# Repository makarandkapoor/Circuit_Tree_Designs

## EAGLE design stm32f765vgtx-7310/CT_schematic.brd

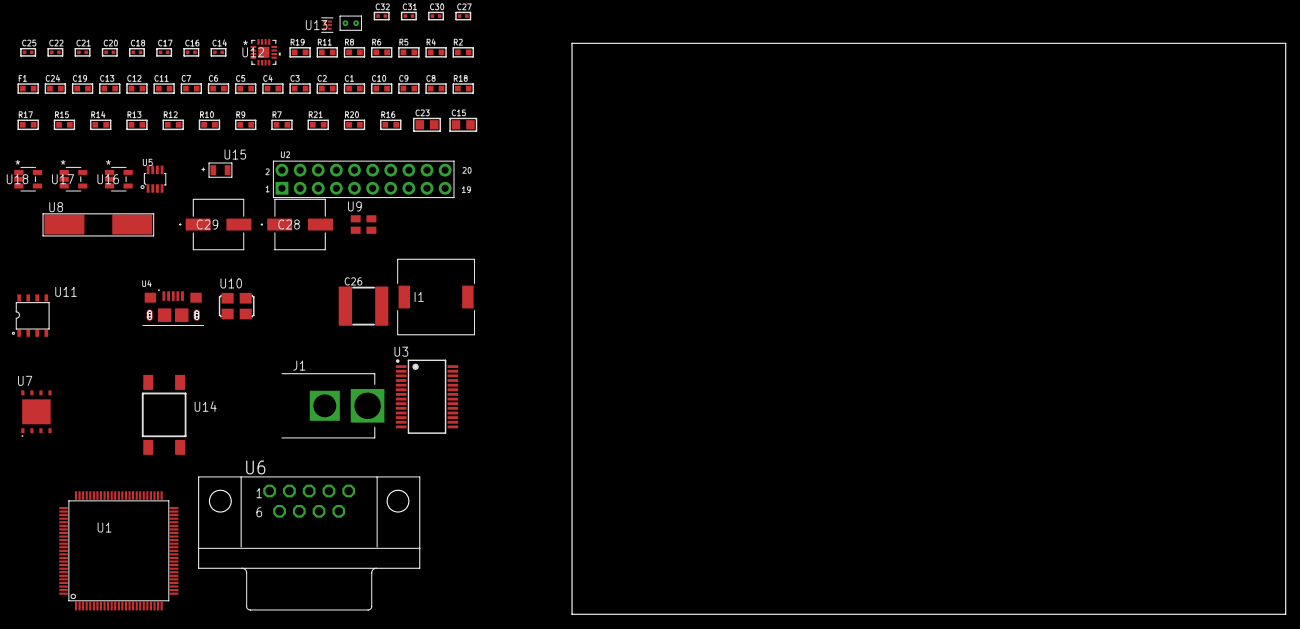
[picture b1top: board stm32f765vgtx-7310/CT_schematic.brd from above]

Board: 2 copper layers, 73 parts (0 on the bottom side), 57 nets, no tracks yet.

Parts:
C1, C12, C13, C19, C24: 1e-06; C0603
C2, C3, C4, C5, C6, C7: 1e-07; C0603
C8: 4.7e-06; C0603
C9, C10: 2.2e-06; C0603
C11: 1e-08; C0603
C14, C16, C17, C18, C25, C27: 1e-07; C0402
C15: 4.7e-06; C0805
C20, C21, C22, C30, C31, C32: 1e-08; C0402
C23: 1e-05; C0805
C26: 6.8e-05; 2220
C28, C29: 0.0001; EXV-9H
F1: 240.0; L0603
I1: 3.8e-06; DR1040
J1: PJ-037B; PJ-037B_PACKAGE
R2: 1000.0; R0603
R4, R5, R6, R8: 4700.0; R0603
R7, R9, R10, R12, R13, R17, R18: 10000.0; R0603
R11: 120.0; R0603
R14: 20000.0; R0603
R15: 91000.0; R0603
R16: 300000.0; R0603
R19: 9100.0; R0603
R20: 680000.0; R0603
R21: 120000.0; R0603
U1: STM32F765VGT6; LQFP100
U2: arducam_ov2640; ARDUCAM
U3: FT232RL-REEL; SSOP-28
U4: 10118193-0001LF; FCI_10118193-0001LF
U5: MAX3051EKA+T; SOT-23-8
U6: 182-009-113R531; 182-009-MALE
U7: MX25R6435FZAIH0; WSON-8-PAD
U8: ABLS-12.000MHZ-B4-T
U9: ASEK-32.768KHz-ECST; ASEK
U10: ASFL1-25MHZ-NCS; ASFL1
U11: idt74fct38072; IDT74FCT38072
U12: LTC3601EUD#PBF; QFN-16_EP
U13: TPS3895ADRYR; SON-6
U14: 4-1437565-2; SW_4-1437565-2
U15: Q65110A2395; LGM67K-G1J2-24-Z
U16, U17, U18: nc7sz125m5x; NC7SZ125M5X
U19: Dummy; DUMMY_PACKAGE_160

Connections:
CLK_CRYSTAL_U3_27: U3.27, U8.1
CLK_CRYSTAL_U3_28: U3.28, U8.2
CLK_U1_8: U1.8, U9.3
CLK_U1_12: U1.12, U11.6
CLK_U2_8: U2.8, U11.7
CLK_U11_3: U10.3, U11.3
GND: C1.2, C2.2, C3.2, C4.2, C5.2, C6.2, C7.2, C8.2, C9.2, C10.2, C11.2, C12.2, C13.2, C14.2, C15.2, C16.2, C17.2, C18.2, C19.2, C20.2, C21.2, C22.2, C23.2, C24.2, C26.1, C26.2, C27.2, C28.2, C29.2, C30.2, C31.2, C32.2, J1.2, R2.2, R7.2, R10.2, R14.2, R16.2, R19.2, R21.2, U1.10, U1.19, U1.26, U1.49, U1.74, U1.99, U2.2, U2.20, U3.7, U3.18, U3.21, U3.25, U3.26, U4.5, U4.6, U4.7, U4.8, U4.9, U5.2, U5.8, U6.5, U7.4, U7.PAD, U9.2, U10.2, U11.4, U11.5, U11.8, U12.1, U12.9, U12.17, U13.2, U15.C, U16.1, U16.3, U17.1, U17.3, U18.1, U18.3, U19.1
NET_U1_14: R5.1, U1.14, U17.4
NET_U1_21: C11.1, C12.1, F1.1, U1.20, U1.21
NET_U1_48: C9.1, U1.48
NET_U1_73: C10.1, U1.73
NET_U1_94: R7.1, U1.94
NET_U1_98: U14.3, U14.4
NET_U2_19: R6.1, U2.19, U18.4
NET_U3_14: R9.1, U3.14
NET_U3_17: C16.1, U3.17
NET_U3_19: R10.1, U3.19
NET_U4_1: R8.1, U4.1
NET_U4_2: U3.16, U4.2
NET_U4_3: U3.15, U4.3
NET_U5_6: R11.2, U5.6
NET_U6_2: R11.2, U5.6, U6.2
NET_U6_3: R11.1, U5.7, U6.3
NET_U7_7: R4.1, U1.23, U7.7, U16.4
NET_U12_3: C25.2, I1.1, U12.3, U12.4
NET_U12_6: C25.1, U12.6
NET_U12_7: C24.1, U12.7, U12.12
NET_U12_10: R16.1, U12.10
NET_U12_11: R14.1, R15.1, U12.11
NET_U12_ATNET_3: I1.2, R15.2
NET_U13_1: R18.1, R19.1, U13.1
NET_U13_3: R20.2, R21.1, U13.3
NET_U13_4: R17.1, U13.4, U16.2, U17.2, U18.2
NET_U14_1: R2.1, U14.1, U14.2
PROC_CAN1_RX: U1.70, U5.4
PROC_CAN1_TX: U1.71, U5.1
PROC_DAC_OUT2: U1.29, U19.2
PROC_DCMI_D0: U1.63, U2.18
PROC_DCMI_D1: U1.64, U2.17
PROC_DCMI_D2: U1.65, U2.16
PROC_DCMI_D3: U1.66, U2.15
PROC_DCMI_D4: U1.3, U2.14
PROC_DCMI_D5: U1.84, U2.13
PROC_DCMI_D6: U1.4, U2.12
PROC_DCMI_D7: U1.5, U2.11
PROC_DCMI_D8: U1.78, U2.10
PROC_DCMI_D9: U1.80, U2.9
PROC_DCMI_HSYNC: U1.28, U2.6
PROC_DCMI_PIXCLK: U1.30, U2.7
PROC_DCMI_VSYNC: U1.93, U2.5
PROC_QUADSPI_BK1_IO0: U1.58, U7.5
PROC_QUADSPI_BK1_IO1: U1.59, U7.2
PROC_QUADSPI_BK1_IO2: R13.1, U1.1, U7.3
PROC_QUADSPI_BK1_NCS: R12.1, U1.46, U7.1
PROC_QUADSPI_CLK: U1.36, U7.6
VCC_S1_8V7: C23.1, C28.1, C29.1, J1.1, U12.15, U12.16
VCC_TIER1_3V3: C1.1, C2.1, C3.1, C4.1, C5.1, C6.1, C7.1, C8.1, C13.1, C14.1, C15.1, C17.1, C18.1, C19.1, C20.1, C21.1, C22.1, C26.2, C27.1, C30.1, C31.1, C32.1, F1.2, I1.2, R4.2, R5.2, R6.2, R9.2, R12.2, R13.2, R15.2, R17.2, R18.2, R20.1, U1.6, U1.11, U1.27, U1.50, U1.75, U1.100, U2.1, U3.4, U3.20, U5.3, U7.8, U9.4, U10.4, U11.1, U11.2, U12.8, U13.6, U16.5, U17.5, U18.5

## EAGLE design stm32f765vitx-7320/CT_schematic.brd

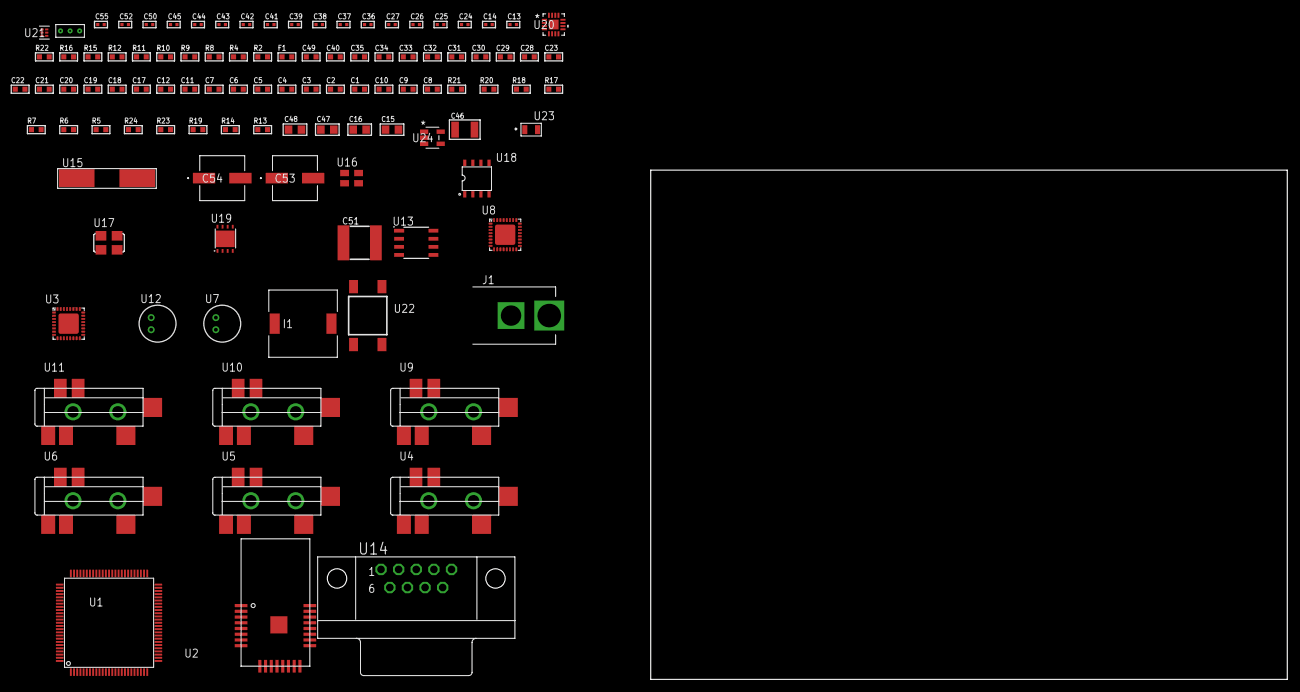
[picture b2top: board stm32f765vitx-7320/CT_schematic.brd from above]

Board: 2 copper layers, 100.0 x 80.0 mm, 105 parts (0 on the bottom side), 75 nets, no tracks yet.

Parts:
C1, C12, C17, C18, C19, C20, C21, C22, C23, C28, C29, C30, C31, C32, C33, C34, C35, C40, C49: 1e-06; C0603
C2, C3, C4, C5, C6, C7: 1e-07; C0603
C8: 4.7e-06; C0603
C9, C10: 2.2e-06; C0603
C11: 1e-08; C0603
C13, C14: 1e-11; C0402
C15, C16, C47, C48: 1e-05; C0805
C24, C25, C26, C27, C36, C37, C38, C39, C41, C50, C52: 1e-07; C0402
C42, C43, C44, C45, C55: 1e-08; C0402
C46: 1e-05; C1210
C51: 6.8e-05; 2220
C53, C54: 0.0001; EXV-9H
F1: 240.0; L0603
I1: 3.8e-06; DR1040
J1: PJ-037B; PJ-037B_PACKAGE
R2, R16: 1000.0; R0603
R4: 4700.0; R0603
R5, R6, R7, R20, R21: 10000.0; R0603
R8, R9, R10, R11: 1270.0; R0603
R12: 120.0; R0603
R13, R14: 100000.0; R0603
R15: 200.0; R0603
R17: 20000.0; R0603
R18: 91000.0; R0603
R19: 300000.0; R0603
R22: 9100.0; R0603
R23: 680000.0; R0603
R24: 120000.0; R0603
U1: STM32F765VIT6; LQFP100
U2: ATBTLC1000-MR110CA
U3, U8: SGTL5000XNAA3; QFN-32
U4, U5, U6, U9, U10, U11: SJ-43515TS-SMT-TR
U7, U12: WM-64PCT; WM-64PC
U13: SN65HVD230D; SOIC-8
U14: 182-009-113R531; 182-009-MALE
U15: ABLS-25.000MHZ-B2F-T
U16: ASEK-32.768KHz-ECST; ASEK
U17: ASFL-24.57MHZ-NCS; ASFL1
U18: idt74fct38072; IDT74FCT38072
U19: LP3878SDX-ADJ/NOPB; WSON-8
U20: LTC3601EUD#PBF; QFN-16_EP
U21: TPS3895ADRYR; SON-6
U22: 4-1437565-2; SW_4-1437565-2
U23: Q65110A2395; LGM67K-G1J2-24-Z
U24: nc7sz125m5x; NC7SZ125M5X
U25: Dummy; DUMMY_PACKAGE_213

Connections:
CLK_CRYSTAL_U1_12: C13.1, U1.12, U15.1
CLK_CRYSTAL_U1_13: C14.1, U1.13, U15.2
CLK_U1_8: U1.8, U16.3
CLK_U3_21: U3.21, U18.7
CLK_U8_21: U8.21, U18.6
CLK_U18_3: U17.3, U18.3
GND: C1.2, C2.2, C3.2, C4.2, C5.2, C6.2, C7.2, C8.2, C9.2, C10.2, C11.2, C12.2, C13.2, C14.2, C15.2, C16.2, C24.2, C25.2, C26.2, C27.2, C28.2, C36.2, C37.2, C38.2, C39.2, C40.2, C41.2, C42.2, C43.2, C44.2, C45.2, C46.2, C47.2, C48.2, C49.2, C51.1, C51.2, C52.2, C53.2, C54.2, C55.2, J1.2, R2.2, R5.2, R9.2, R11.2, R13.2, R16.2, R17.2, R19.2, R22.2, R24.2, U1.10, U1.19, U1.26, U1.49, U1.74, U1.99, U2.1, U2.9, U2.13, U2.24, U2.25, U3.1, U3.3, U3.7, U3.EXP, U5.1, U6.1, U7.2, U8.1, U8.3, U8.7, U8.EXP, U10.1, U11.1, U12.2, U13.2, U14.5, U16.2, U17.2, U18.4, U18.5, U18.8, U19.3, U19.PAD, U20.1, U20.9, U20.17, U21.2, U23.C, U24.1, U24.3, U25.1
NET_U1_14: R4.1, U1.14, U24.4
NET_U1_21: C11.1, C12.1, F1.1, U1.20, U1.21
NET_U1_48: C9.1, U1.48
NET_U1_73: C10.1, U1.73
NET_U1_94: R5.1, U1.94
NET_U1_98: U22.3, U22.4
NET_U2_17: R6.1, U2.17
NET_U2_20: R7.1, U2.20
NET_U3_10: C27.1, U3.10
NET_U3_29: R8.1, U3.29
NET_U3_31: R9.1, U3.31
NET_U4_1: U3.4, U4.1
NET_U4_2: U3.2, U4.2
NET_U4_5: U3.6, U4.5
NET_U5_2: C18.1, U5.2
NET_U5_5: C17.1, U5.5
NET_U6_2: C20.1, C21.1, U6.2
NET_U6_5: C19.1, U6.5
NET_U6_13: C20.2, C21.2
NET_U7_1: C22.1, C23.1, C28.1, U3.16, U7.1
NET_U7_15: C22.2, C23.2
NET_U8_10: C39.1, U8.10
NET_U8_29: R10.1, U8.29
NET_U8_31: R11.1, U8.31
NET_U9_1: U8.4, U9.1
NET_U9_2: U8.2, U9.2
NET_U9_5: U8.6, U9.5
NET_U10_2: C30.1, U10.2
NET_U10_5: C29.1, U10.5
NET_U11_2: C32.1, C33.1, U11.2
NET_U11_5: C31.1, U11.5
NET_U11_13: C32.2, C33.2
NET_U12_1: C34.1, C35.1, C40.1, U8.16, U12.1
NET_U12_15: C34.2, C35.2
NET_U13_6: R12.2, U13.6
NET_U13_8: R13.1, U13.8
NET_U14_2: R12.2, U13.6, U14.2
NET_U14_3: R12.1, U13.7, U14.3
NET_U19_1: C45.1, U19.1
NET_U19_6: R15.2, R16.1, U19.6
NET_U19_8: R14.1, U19.8
NET_U20_3: C50.2, I1.1, U20.3, U20.4
NET_U20_6: C50.1, U20.6
NET_U20_7: C49.1, U20.7, U20.12
NET_U20_10: R19.1, U20.10
NET_U20_11: R17.1, R18.1, U20.11
NET_U20_ATNET_3: I1.2, R18.2
NET_U21_1: R21.1, R22.1, U21.1
NET_U21_3: R23.2, R24.1, U21.3
NET_U21_4: R20.1, U21.4, U24.2
NET_U22_1: R2.1, U22.1, U22.2
PROC_ADC1_IN3: U1.25, U25.2
PROC_ADC1_IN12: U1.17, U25.3
PROC_CAN1_RX: U1.70, U13.4
PROC_CAN1_TX: U1.71, U13.1
PROC_I2S1_CK: U1.29, U3.24
PROC_I2S1_SD: U1.31, U3.26
PROC_I2S1_WS: U1.28, U3.23
PROC_I2S2_CK: U1.46, U8.24
PROC_I2S2_SD: U1.16, U8.26
PROC_I2S2_WS: U1.51, U8.23
PROC_SPI1_MISO: U1.30, U2.14
PROC_SPI1_MOSI: U1.88, U2.11
PROC_SPI1_NSS: U1.77, U2.12
PROC_SPI1_SCK: U1.89, U2.10
VCC_S1_11V4: C46.1, C48.1, C53.1, C54.1, J1.1, R14.2, U19.4, U20.15, U20.16
VCC_TIER1_1V2: C24.1, C36.1, C47.1, R15.1, U3.30, U8.30, U19.5
VCC_TIER1_3V3: C1.1, C2.1, C3.1, C4.1, C5.1, C6.1, C7.1, C8.1, C15.1, C16.1, C25.1, C26.1, C37.1, C38.1, C41.1, C42.1, C43.1, C44.1, C51.2, C52.1, C55.1, F1.2, I1.2, R4.2, R6.2, R7.2, R8.2, R10.2, R18.2, R20.2, R21.2, R23.1, U1.6, U1.11, U1.27, U1.50, U1.75, U1.100, U2.6, U2.22, U3.5, U3.20, U8.5, U8.20, U13.3, U16.4, U17.4, U18.1, U18.2, U20.8, U21.6, U24.5

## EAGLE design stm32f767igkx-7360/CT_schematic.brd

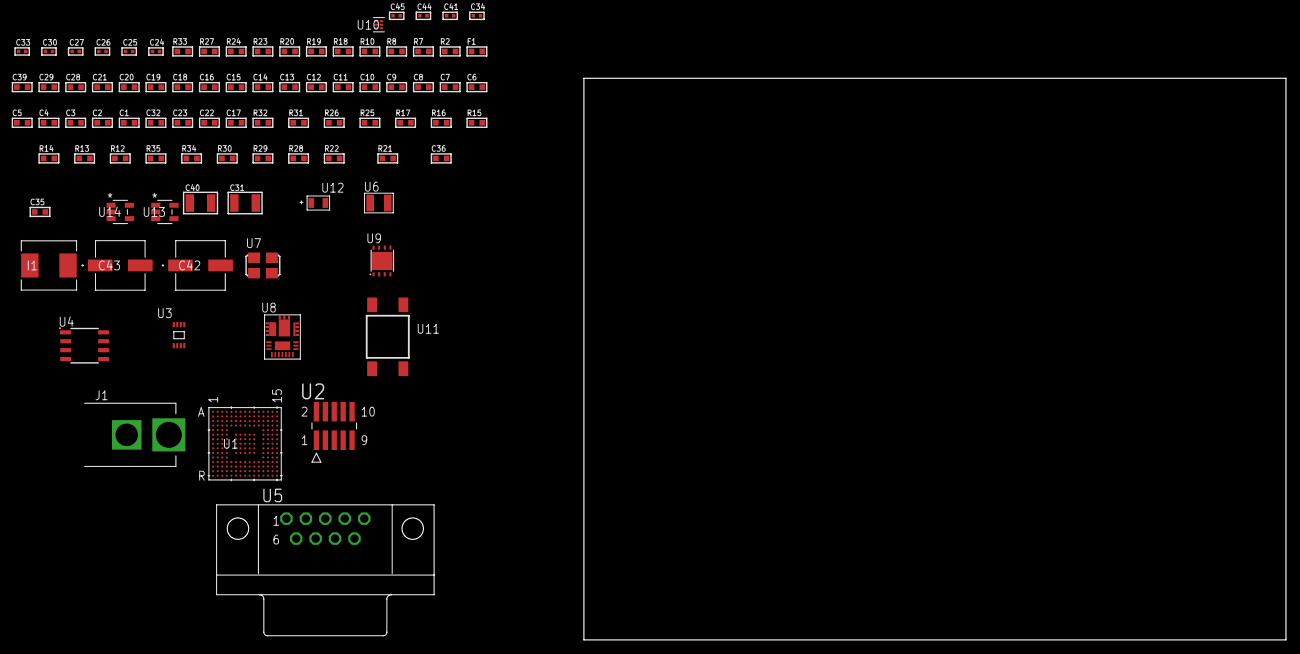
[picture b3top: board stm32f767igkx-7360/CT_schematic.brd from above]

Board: 2 copper layers, 100.0 x 80.0 mm, 88 parts (0 on the bottom side), 43 nets, no tracks yet.

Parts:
C1, C20, C28, C29: 1e-06; C0603
C2, C3, C4, C5, C6, C7, C8, C9, C10, C11, C12, C13, C14, C15, C16, C18, C21: 1e-07; C0603
C17: 4.7e-06; C0603
C19: 1e-08; C0603
C22, C23, C32: 2.2e-06; C0603
C24, C25: 1e-11; C0402
C26, C33, C34, C41: 1e-07; C0402
C27, C30, C44, C45: 1e-08; C0402
C31: 0.0001; C1210
C35: 6.9430689229727e-09; R0603
C36: 2.3669553146498e-07; R0603
C39: 8e-07; R0603
C40: 1e-05; C1210
C42, C43: 0.0001; EXV-9H
F1: 240.0; L0603
I1: 6.8e-07; IND25X25CZ
J1: PJ-037B; PJ-037B_PACKAGE
R2: 1000.0; R0603
R7: 4700.0; R0603
R8, R10: 2200.0; R0603
R12, R13, R14, R15, R16, R17, R31, R32: 10000.0; R0603
R18: 5.0; R0603
R19: 120.0; R0603
R20: 0.1; R0603
R21: 4030.2416170974; R0603
R22: 719.68600305311; R0603
R23: 75.0; R0603
R24: 130.0; R0603
R25: 39000.0; R0603
R26: 49900.0; R0603
R27: 5760.0; R0603
R28, R30: 100000.0; R0603
R29: 300000.0; R0603
R33: 9100.0; R0603
R34: 680000.0; R0603
R35: 120000.0; R0603
U1: STM32F767IGK6; UFBGA176_25
U2: FTSH-105-01-L-DV-K; SAMTEC_FTSH-105-01-L-DV-K
U3: 24AA01T-I/MNY; TDFN-8/6MM
U4: MCP2562-E/SN; SOIC-8
U5: 182-009-113R531; 182-009-MALE
U6: ABS07-32.768KHZ-7-T
U7: ASFL1-25MHZ-NCS; ASFL1
U8: IR3899MTR1PBF
U9: LP2951ACSDX/NOPB; WSON-8
U10: TPS3895ADRYR; SON-6
U11: 4-1437565-2; SW_4-1437565-2
U12: Q65110A2395; LGM67K-G1J2-24-Z
U13, U14: nc7sz125m5x; NC7SZ125M5X

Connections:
CLK_CRYSTAL_U1_E1: C24.1, U1.E1, U6.1
CLK_CRYSTAL_U1_F1: C25.1, U1.F1, U6.2
CLK_U1_G1: U1.G1, U7.3
GND: C1.2, C2.2, C3.2, C4.2, C5.2, C6.2, C7.2, C8.2, C9.2, C10.2, C11.2, C12.2, C13.2, C14.2, C15.2, C16.2, C17.2, C18.2, C19.2, C20.2, C21.2, C22.2, C23.2, C24.2, C25.2, C26.2, C27.2, C28.2, C29.2, C30.2, C32.2, C33.2, C34.2, C39.2, C40.2, C41.2, C42.2, C43.2, C44.2, C45.2, J1.2, R2.2, R12.2, R14.2, R18.2, R20.1, R20.2, R22.2, R25.2, R27.2, R30.2, R33.2, R35.2, U1.D5, U1.D7, U1.D8, U1.D9, U1.F2, U1.F6, U1.F7, U1.F8, U1.F9, U1.F10, U1.F12, U1.G2, U1.G6, U1.G7, U1.G8, U1.G9, U1.G10, U1.G12, U1.H6, U1.H7, U1.H8, U1.H9, U1.H10, U1.H12, U1.J6, U1.J7, U1.J8, U1.J9, U1.J10, U1.K6, U1.K7, U1.K8, U1.K9, U1.K10, U1.M1, U1.M8, U1.M9, U1.N1, U2.3, U2.5, U3.4, U3.7, U4.2, U4.8, U5.5, U7.2, U8.4, U8.11, U8.17, U9.3, U9.4, U9.PAD, U10.2, U12.C, U13.2, U13.3, U14.1, U14.3
NET_U1_A5: R8.1, U1.A5, U3.6
NET_U1_B4: R10.1, U1.B4, U3.5
NET_U1_C6: R13.1, U1.C6
NET_U1_D6: R12.1, U1.D6
NET_U1_F13: C23.1, U1.F13
NET_U1_J1: R7.1, U1.J1, U14.4
NET_U1_L4: R14.1, U1.L4
NET_U1_M10: C22.1, U1.M10
NET_U1_R1: C19.1, C20.1, F1.1, U1.P1, U1.R1
NET_U1_R15: U11.3, U11.4
NET_U2_9: R18.1, U2.9
NET_U4_6: R19.2, U4.6
NET_U5_2: R19.2, U4.6, U5.2
NET_U5_3: R19.1, U4.7, U5.3
NET_U8_1: C35.1, R21.1, R22.1, R23.1, R24.1, U8.1, U8.8
NET_U8_2: C34.1, U8.2
NET_U8_3: C35.2, C36.1, C36.2, U8.3
NET_U8_5: R25.1, U8.5
NET_U8_10: C32.1, U8.10
NET_U8_12: C31.1, I1.1, U8.12
NET_U8_14: C31.2, U8.14
NET_U8_15: R26.1, R27.1, U8.15
NET_U8_ATNET_3: I1.2, R21.2
NET_U8_ATNET_4: C36.2, R23.2
NET_U9_5: R28.1, U9.5
NET_U9_7: R29.2, R30.1, U9.7
NET_U10_1: R32.1, R33.1, U10.1
NET_U10_3: R34.2, R35.1, U10.3
NET_U10_4: R31.1, U10.4, U13.4, U14.2
NET_U11_1: R2.1, U11.1, U11.2
PROC_CAN1_RX: U1.B12, U4.4
PROC_CAN1_TX: U1.B15, U4.1
PROC_SYS_JTCK_SWCLK: R16.1, U1.A14, U2.4
PROC_SYS_JTDO_SWO: U1.A10, U2.6
PROC_SYS_JTMS_SWDIO: R17.1, U1.A15, U2.2
RST_OUT_U2_JTAG_RST_B: R15.1, U2.10, U13.1
VCC_S1_15V2: C33.1, C39.1, C42.1, C43.1, J1.1, R26.2, U8.9, U9.8
VCC_TIER1_3V3: C1.1, C2.1, C3.1, C4.1, C5.1, C6.1, C7.1, C8.1, C9.1, C10.1, C11.1, C12.1, C13.1, C14.1, C15.1, C16.1, C17.1, C18.1, C21.1, C26.1, C27.1, C29.1, C30.1, C41.1, C44.1, C45.1, F1.2, I1.2, R7.2, R8.2, R10.2, R13.2, R15.2, R16.2, R17.2, R21.2, R31.2, R32.2, R34.1, U1.C1, U1.C5, U1.C7, U1.C8, U1.C9, U1.F3, U1.G3, U1.G13, U1.H13, U1.J12, U1.J13, U1.K4, U1.N8, U1.N9, U1.N10, U2.1, U3.8, U4.5, U7.4, U10.6, U13.5, U14.5
VCC_TIER1_5V0: C28.1, C40.1, R28.2, R29.1, U4.3, U9.1

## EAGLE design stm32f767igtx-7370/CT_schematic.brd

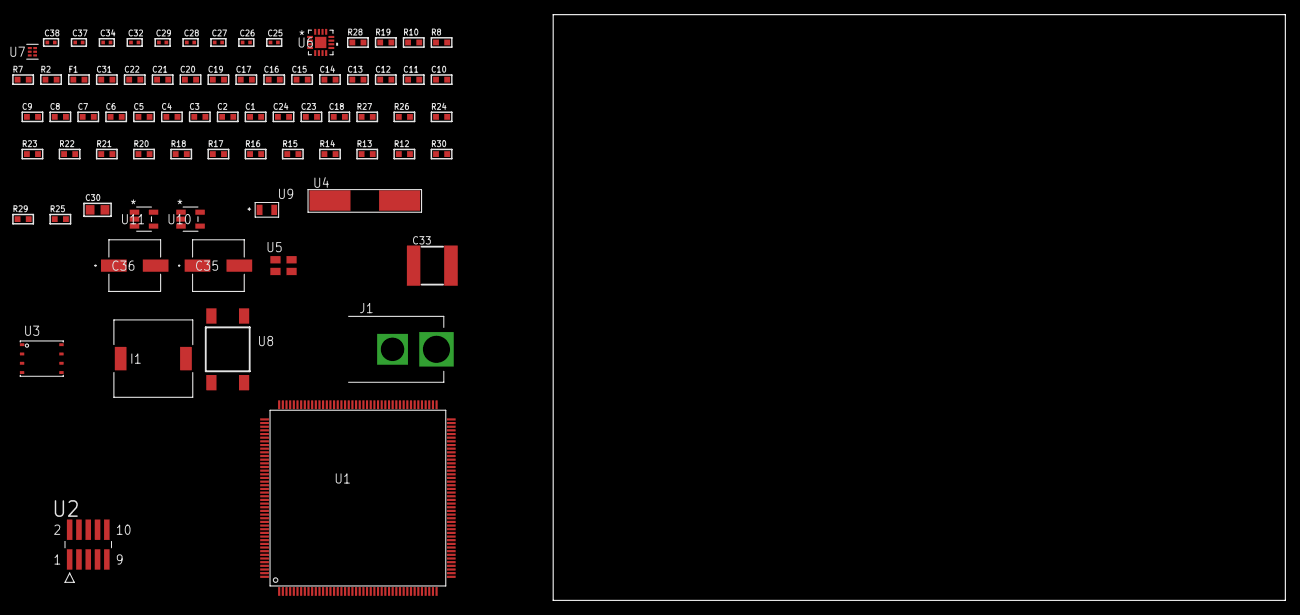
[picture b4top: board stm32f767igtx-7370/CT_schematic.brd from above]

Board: 2 copper layers, 100.0 x 80.0 mm, 75 parts (0 on the bottom side), 35 nets, no tracks yet.

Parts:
C1, C21, C31: 1e-06; C0603
C2, C3, C4, C5, C6, C7, C8, C9, C10, C11, C12, C13, C14, C15, C16, C17, C19, C22: 1e-07; C0603
C18: 4.7e-06; C0603
C20: 1e-08; C0603
C23, C24: 2.2e-06; C0603
C25, C26: 1e-11; C0402
C27, C32, C34: 1e-07; C0402
C28, C29, C37, C38: 1e-08; C0402
C30: 1e-05; C0805
C33: 6.8e-05; 2220
C35, C36: 0.0001; EXV-9H
F1: 240.0; L0603
I1: 5.2e-06; DR1040
J1: PJ-037B; PJ-037B_PACKAGE
R2: 1000.0; R0603
R7: 4700.0; R0603
R8, R10: 2200.0; R0603
R12, R13, R14, R15, R16, R17, R18, R20, R21, R22, R26, R27: 10000.0; R0603
R19: 5.0; R0603
R23: 20000.0; R0603
R24: 91000.0; R0603
R25: 300000.0; R0603
R28: 9100.0; R0603
R29: 680000.0; R0603
R30: 120000.0; R0603
U1: STM32F767IGT6; LQFP176
U2: FTSH-105-01-L-DV-K; SAMTEC_FTSH-105-01-L-DV-K
U3: 24AA512-I/MF; DFN8-S
U4: ABLS-25.000MHZ-B2F-T
U5: ASEK-32.768KHz-ECST; ASEK
U6: LTC3601EUD#PBF; QFN-16_EP
U7: TPS3895ADRYR; SON-6
U8: 4-1437565-2; SW_4-1437565-2
U9: Q65110A2395; LGM67K-G1J2-24-Z
U10, U11: nc7sz125m5x; NC7SZ125M5X

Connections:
CLK_CRYSTAL_U1_29: C25.1, U1.29, U4.1
CLK_CRYSTAL_U1_30: C26.1, U1.30, U4.2
CLK_U1_9: U1.9, U5.3
GND: C1.2, C2.2, C3.2, C4.2, C5.2, C6.2, C7.2, C8.2, C9.2, C10.2, C11.2, C12.2, C13.2, C14.2, C15.2, C16.2, C17.2, C18.2, C19.2, C20.2, C21.2, C22.2, C23.2, C24.2, C25.2, C26.2, C27.2, C28.2, C29.2, C30.2, C31.2, C33.1, C33.2, C34.2, C35.2, C36.2, C37.2, C38.2, J1.2, R2.2, R12.2, R14.2, R18.2, R19.2, R21.2, R23.2, R25.2, R28.2, R30.2, U1.14, U1.22, U1.37, U1.61, U1.71, U1.90, U1.102, U1.113, U1.126, U1.135, U1.148, U1.158, U2.3, U2.5, U3.4, U3.7, U5.2, U6.1, U6.9, U6.17, U7.2, U9.C, U10.2, U10.3, U11.1, U11.3
NET_U1_31: R7.1, U1.31, U11.4
NET_U1_39: C20.1, C21.1, F1.1, U1.38, U1.39
NET_U1_48: R14.1, U1.48
NET_U1_81: C23.1, U1.81
NET_U1_125: C24.1, U1.125
NET_U1_164: R8.1, U1.164, U3.6
NET_U1_165: R10.1, U1.165, U3.5
NET_U1_166: R12.1, U1.166
NET_U1_171: R13.1, U1.171
NET_U1_176: U8.3, U8.4
NET_U2_9: R19.1, U2.9
NET_U3_1: R20.1, U3.1
NET_U3_2: R21.1, U3.2
NET_U3_3: R22.1, U3.3
NET_U6_3: C32.2, I1.1, U6.3, U6.4
NET_U6_6: C32.1, U6.6
NET_U6_7: C31.1, U6.7, U6.12
NET_U6_10: R25.1, U6.10
NET_U6_11: R23.1, R24.1, U6.11
NET_U6_ATNET_3: I1.2, R24.2
NET_U7_1: R27.1, R28.1, U7.1
NET_U7_3: R29.2, R30.1, U7.3
NET_U7_4: R26.1, U7.4, U10.4, U11.2
NET_U8_1: R2.1, U8.1, U8.2
PROC_SYS_JTCK_SWCLK: R18.1, U1.137, U2.4
PROC_SYS_JTDI: R16.1, U1.138, U2.8
PROC_SYS_JTDO_SWO: U1.161, U2.6
PROC_SYS_JTMS_SWDIO: R17.1, U1.124, U2.2
RST_OUT_U2_JTAG_RST_B: R15.1, U2.10, U10.1
VCC_S1_9V2: C30.1, C35.1, C36.1, J1.1, U6.15, U6.16
VCC_TIER1_3V3: C1.1, C2.1, C3.1, C4.1, C5.1, C6.1, C7.1, C8.1, C9.1, C10.1, C11.1, C12.1, C13.1, C14.1, C15.1, C16.1, C17.1, C18.1, C19.1, C22.1, C27.1, C28.1, C29.1, C33.2, C34.1, C37.1, C38.1, F1.2, I1.2, R7.2, R8.2, R10.2, R13.2, R15.2, R16.2, R17.2, R20.2, R22.2, R24.2, R26.2, R27.2, R29.1, U1.6, U1.15, U1.23, U1.36, U1.49, U1.62, U1.72, U1.82, U1.91, U1.103, U1.114, U1.127, U1.136, U1.149, U1.159, U1.172, U2.1, U3.8, U5.4, U6.8, U7.6, U10.5, U11.5

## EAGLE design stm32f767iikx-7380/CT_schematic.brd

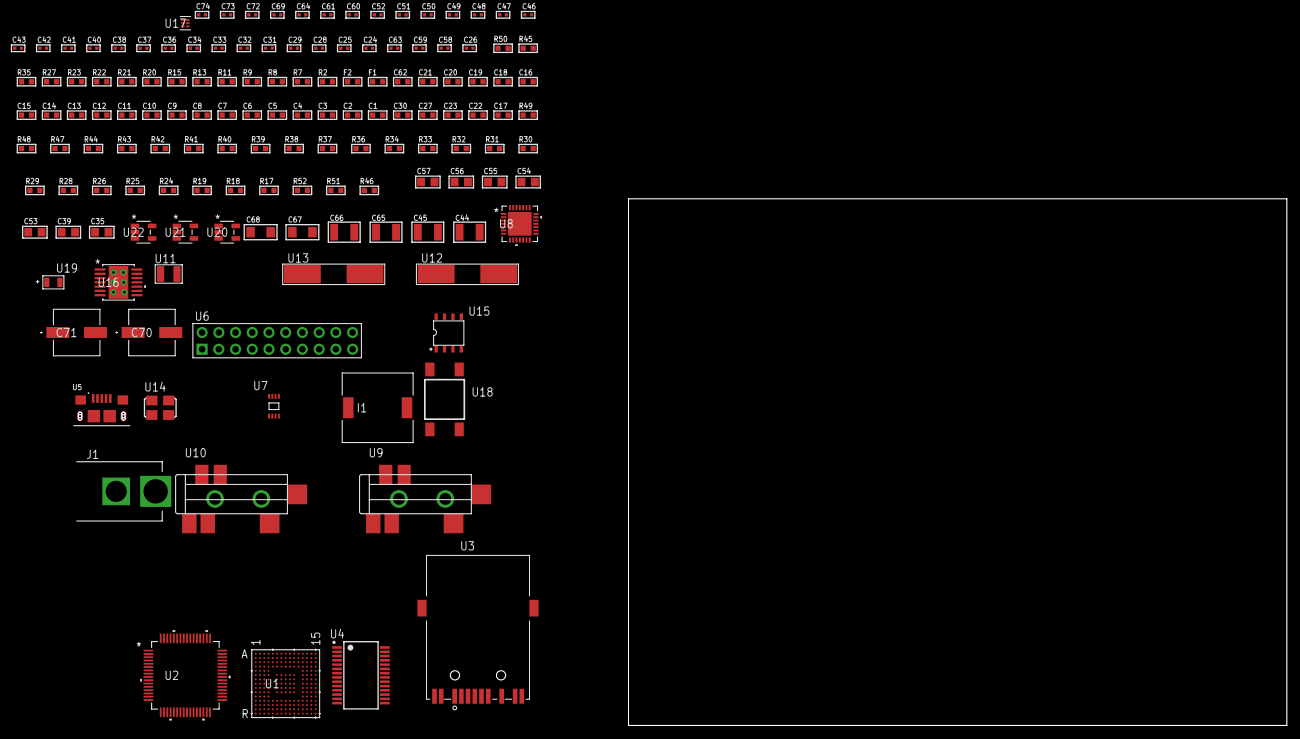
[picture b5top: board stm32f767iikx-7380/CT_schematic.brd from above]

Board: 2 copper layers, 143 parts (0 on the bottom side), 97 nets, no tracks yet.

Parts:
C1, C20, C62: 1e-06; C0603
C2, C3, C4, C5, C6, C7, C8, C9, C10, C11, C12, C13, C14, C15, C16, C18, C21: 1e-07; C0603
C17: 4.7e-06; C0603
C19: 1e-08; C0603
C22, C23, C27, C30: 2.2e-06; C0603
C24, C25: 1e-11; C0402
C26: 1.8e-08; C0402
C28, C31, C33, C34, C36, C37, C38, C40, C41, C42, C48, C49, C50, C51, C52, C64, C69: 1e-07; C0402
C29, C32, C43, C60, C61, C72, C73, C74: 1e-08; C0402
C35, C53, C54, C55, C56, C57: 1e-05; C0805
C39: 4.7e-06; C0805
C44, C45, C65, C66: 2.2e-05; C1210
C46, C47: 1e-09; C0402
C58, C59: 2.2e-11; C0402
C63: 3.3e-09; C0402
C67, C68: 1e-05; C1206
C70, C71: 0.0001; EXV-9H
F1: 240.0; L0603
F2: 510.0; L0603
I1: 5.2e-06; DR1040
J1: PJ-037B; PJ-037B_PACKAGE
R2: 1000.0; R0603
R7, R8, R35: 4700.0; R0603
R9, R11, R13, R15: 2200.0; R0603
R17, R18, R19, R24, R25, R26, R28, R29, R30, R31, R32, R33, R34, R36, R37, R38, R39, R40, R41, R48, R49: 10000.0; R0603
R20, R21: 0.1; R0603
R22, R23: 200.0; R0603
R27: 1270.0; R0603
R42, R43, R44: 47000.0; R0603
R45: 680.0; R0603
R46: 71007.101651032; R0603
R47: 22000.0; R0603
R50: 9100.0; R0603
R51: 680000.0; R0603
R52: 120000.0; R0603
U1: STM32F767IIK6; UFBGA176_25
U2: BCM5221KPT; TQFP64_10X10MC
U3: 7498011122R
U4: FT232RL-REEL; SSOP-28
U5: 10118193-0001LF; FCI_10118193-0001LF
U6: TST-110-05-T-D-RA
U7: 24AA64T-I/MNY; TDFN-8/6MM
U8: WM8731CLSEFL; QFN-28
U9, U10: SJ-43515TS-SMT-TR
U11: ABS07-32.768KHZ-7-T
U12: ABLS-12.000MHZ-B4-T
U13: ABLS-12.288MHZ-B4-T
U14: ASFL1-25MHZ-NCS; ASFL1
U15: idt74fct38072; IDT74FCT38072
U16: tps54225PWP; HTSSOP14
U17: TPS3895ADRYR; SON-6
U18: 4-1437565-2; SW_4-1437565-2
U19: Q65110A2395; LGM67K-G1J2-24-Z
U20, U21, U22: nc7sz125m5x; NC7SZ125M5X

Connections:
CLK_CRYSTAL_U1_E1: C24.1, U1.E1, U11.1
CLK_CRYSTAL_U1_F1: C25.1, U1.F1, U11.2
CLK_CRYSTAL_U4_27: U4.27, U12.1
CLK_CRYSTAL_U4_28: U4.28, U12.2
CLK_CRYSTAL_U8_1: C58.1, U8.1, U13.1
CLK_CRYSTAL_U8_2: C59.1, U8.2, U13.2
CLK_U1_G1: U1.G1, U15.7
CLK_U2_4: U2.4, U15.6
CLK_U15_3: U14.3, U15.3
GND: C1.2, C2.2, C3.2, C4.2, C5.2, C6.2, C7.2, C8.2, C9.2, C10.2, C11.2, C12.2, C13.2, C14.2, C15.2, C16.2, C17.2, C18.2, C19.2, C20.2, C21.2, C22.2, C23.2, C24.2, C25.2, C26.2, C27.2, C28.2, C29.2, C30.2, C31.2, C32.2, C33.2, C34.2, C35.2, C36.2, C37.2, C38.2, C39.2, C40.2, C41.2, C42.2, C43.2, C47.2, C48.2, C49.2, C50.2, C51.2, C52.2, C53.2, C54.2, C55.2, C56.2, C57.2, C58.2, C59.2, C60.2, C61.2, C62.2, C63.2, C65.2, C66.2, C67.2, C68.2, C69.2, C70.2, C71.2, C72.2, C73.2, C74.2, J1.2, R2.2, R17.2, R19.2, R20.2, R21.2, R24.2, R26.2, R27.2, R30.2, R31.2, R32.2, R37.2, R42.2, R43.2, R44.2, R47.2, R50.2, R52.2, U1.D5, U1.D7, U1.D8, U1.D9, U1.F2, U1.F6, U1.F7, U1.F8, U1.F9, U1.F10, U1.F12, U1.G2, U1.G6, U1.G7, U1.G8, U1.G9, U1.G10, U1.G12, U1.H6, U1.H7, U1.H8, U1.H9, U1.H10, U1.H12, U1.J6, U1.J7, U1.J8, U1.J9, U1.J10, U1.K6, U1.K7, U1.K8, U1.K9, U1.K10, U1.M1, U1.M8, U1.M9, U1.N1, U2.6, U2.7, U2.24, U2.29, U2.32, U2.40, U2.45, U2.54, U2.63, U3.10, U3.12, U4.7, U4.18, U4.21, U4.25, U4.26, U5.5, U5.6, U5.7, U5.8, U5.9, U6.4, U6.6, U6.8, U6.10, U6.12, U6.14, U6.16, U6.18, U6.20, U7.4, U8.4, U8.15, U8.19, U8.25, U8.26, U8.29, U9.1, U10.1, U14.2, U15.4, U15.5, U15.8, U16.5, U16.8, U16.9, U16.15, U17.2, U19.C, U20.2, U20.3, U21.1, U21.3, U22.1, U22.3
NET_U1_A5: R9.1, U1.A5, U7.6
NET_U1_B4: R11.1, U1.B4, U7.5
NET_U1_C6: R18.1, U1.C6
NET_U1_D6: R17.1, U1.D6
NET_U1_F13: C23.1, U1.F13
NET_U1_J1: R8.1, U1.J1, U22.4
NET_U1_L4: R19.1, U1.L4
NET_U1_M3: R13.1, U1.M3, U2.42
NET_U1_M10: C22.1, U1.M10
NET_U1_P2: R15.1, U1.P2, U2.41
NET_U1_R1: C19.1, C20.1, F1.1, U1.P1, U1.R1
NET_U1_R15: U18.3, U18.4
NET_U2_2: C30.1, C31.1, C32.1, U2.2, U2.55
NET_U2_9: R7.1, U2.9, U21.4
NET_U2_10: R28.1, U2.10
NET_U2_11: R29.1, U2.11
NET_U2_12: R30.1, U2.12
NET_U2_13: R31.1, U2.13
NET_U2_14: R32.1, U2.14
NET_U2_16: R26.1, U2.16
NET_U2_18: R34.1, U2.18
NET_U2_23: R27.1, U2.23
NET_U2_27: C27.1, C28.1, C29.1, U2.22, U2.27, U2.28
NET_U2_37: R33.1, U2.37
NET_U2_38: R24.1, U2.38
NET_U2_39: R25.1, U2.39
NET_U3_1: U2.31, U3.1
NET_U3_2: F2.2, U3.2
NET_U3_3: U2.30, U3.3
NET_U3_4: U2.26, U3.4
NET_U3_5: C26.1, F2.1, U3.2, U3.5
NET_U3_6: U2.25, U3.6
NET_U3_8: R21.1, U3.8
NET_U3_9: R22.1, U3.9
NET_U3_11: R23.1, U3.11
NET_U3_12: R22.2, U3.12
NET_U3_13: R20.1, U3.13, U3.14
NET_U4_14: R36.1, U4.14
NET_U4_17: C40.1, U4.17
NET_U4_19: R37.1, U4.19
NET_U5_1: R35.1, U5.1
NET_U5_2: U4.16, U5.2
NET_U5_3: U4.15, U5.3
NET_U7_1: R39.1, U7.1
NET_U7_2: R40.1, U7.2
NET_U7_3: R41.1, U7.3
NET_U8_20: C52.1, C57.1, U8.20
NET_U9_2: C45.1, R43.1, U9.2
NET_U9_5: C44.1, R42.1, U9.5
NET_U10_5: C46.1, C47.1, R44.1, R45.1, U10.5
NET_U16_2: R46.2, R47.1, U16.2
NET_U16_3: C62.1, U16.3
NET_U16_4: C63.1, U16.4
NET_U16_10: C64.1, I1.1, U16.10, U16.11
NET_U16_12: C64.2, U16.12
NET_U17_1: R49.1, R50.1, U17.1
NET_U17_3: R51.2, R52.1, U17.3
NET_U17_4: R48.1, U17.4, U20.4, U21.2, U22.2
NET_U18_1: R2.1, U18.1, U18.2
PROC_ETH_COL: U1.G4, U2.61
PROC_ETH_CRS: U1.F4, U2.62
PROC_ETH_RXD0: U1.N5, U2.48
PROC_ETH_RXD1: U1.P5, U2.47
PROC_ETH_RXD2: U1.M11, U2.44
PROC_ETH_RXD3: U1.N12, U2.43
PROC_ETH_RX_CLK: U1.N2, U2.50
PROC_ETH_RX_DV: U1.R3, U2.49
PROC_ETH_RX_ER: U1.E3, U2.51
PROC_ETH_TXD0: U1.A8, U2.57
PROC_ETH_TXD1: U1.A7, U2.58
PROC_ETH_TXD2: U1.M4, U2.59
PROC_ETH_TXD3: U1.A2, U2.60
PROC_ETH_TX_CLK: U1.M5, U2.53
PROC_ETH_TX_EN: U1.R13, U2.56
PROC_I2S1_CK: U1.B9, U8.7
PROC_I2S1_SD: U1.A6, U8.8
PROC_I2S1_WS: U1.B10, U8.9, U8.11
PROC_SYS_JTCK_SWCLK: U1.A14, U6.9
PROC_SYS_JTDO_SWO: U1.A10, U6.13
PROC_SYS_JTMS_SWDIO: U1.A15, U6.7
PROC_UART4_CTS: U1.R5, U4.3
PROC_UART4_RTS: U1.A13, U4.11
PROC_UART4_RX: U1.B12, U4.1
PROC_UART4_TX: U1.B14, U4.5
RST_OUT_U6_SRESET_B: R38.1, U6.15, U20.1
VCC_S1_7V4: C67.1, C68.1, C70.1, C71.1, J1.1, U16.7, U16.13, U16.14
VCC_TIER1_3V3: C1.1, C2.1, C3.1, C4.1, C5.1, C6.1, C7.1, C8.1, C9.1, C10.1, C11.1, C12.1, C13.1, C14.1, C15.1, C16.1, C17.1, C18.1, C21.1, C33.1, C34.1, C35.1, C36.1, C37.1, C38.1, C39.1, C41.1, C42.1, C43.1, C48.1, C49.1, C50.1, C51.1, C53.1, C54.1, C55.1, C56.1, C60.1, C61.1, C65.1, C66.1, C69.1, C72.1, C73.1, C74.1, F1.2, I1.2, R7.2, R8.2, R9.2, R11.2, R13.2, R15.2, R18.2, R25.2, R28.2, R29.2, R33.2, R34.2, R36.2, R38.2, R39.2, R40.2, R41.2, R46.1, R48.2, R49.2, R51.1, U1.C1, U1.C5, U1.C7, U1.C8, U1.C9, U1.F3, U1.G3, U1.G13, U1.H13, U1.J12, U1.J13, U1.K4, U1.N8, U1.N9, U1.N10, U2.1, U2.3, U2.46, U4.4, U4.20, U6.1, U7.7, U7.8, U8.3, U8.5, U8.12, U8.18, U14.4, U15.1, U15.2, U16.1, U17.6, U20.5, U21.5, U22.5

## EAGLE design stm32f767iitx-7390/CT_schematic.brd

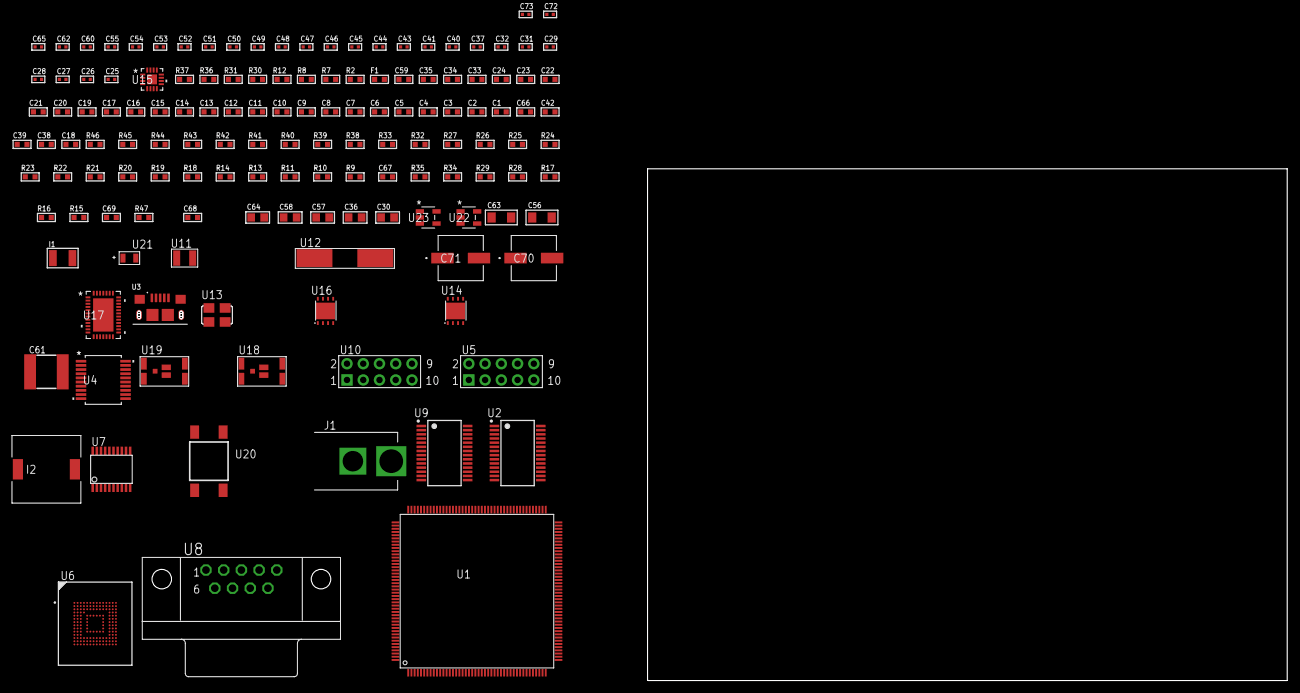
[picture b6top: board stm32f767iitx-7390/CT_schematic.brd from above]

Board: 2 copper layers, 142 parts (0 on the bottom side), 113 nets, no tracks yet.

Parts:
C1, C21, C33, C34, C35, C59: 1e-06; C0603
C2, C3, C4, C5, C6, C7, C8, C9, C10, C11, C12, C13, C14, C15, C16, C17, C19, C22, C23, C24: 1e-07; C0603
C18: 4.7e-06; C0603
C20: 1e-08; C0603
C25, C26, C27, C28: 1e-11; C0402
C29, C31, C32, C37, C40, C41, C43, C44, C45, C46, C47, C48, C49, C50, C51, C52, C53, C60, C65: 1e-07; C0402
C30, C36: 4.7e-06; C0805
C38, C39, C42, C66: 2.2e-06; C0603
C54, C55, C62, C72, C73: 1e-08; C0402
C56, C63: 1e-05; C1206
C57, C58, C64: 1e-05; C0805
C61: 6.8e-05; 2220
C67: 2.45e-08; R0603
C68: 2.8258362168397e-09; R0603
C69: 7.105e-09; R0603
C70, C71: 0.0001; EXV-9H
F1: 240.0; L0603
I1: 1.5e-05; L1210
I2: 3.8e-06; DR1040
J1: PJ-037B; PJ-037B_PACKAGE
R2, R31, R37: 1000.0; R0603
R7, R8, R12: 4700.0; R0603
R9, R10, R11, R13, R14, R38, R40, R41, R44, R45, R46: 10000.0; R0603
R15, R16, R17, R28, R29, R35: 100000.0; R0603
R18, R19, R20, R21, R22, R23, R24, R25, R26, R27: 34000.0; R0603
R30, R36: 200.0; R0603
R32: 20000.0; R0603
R33: 91000.0; R0603
R34: 300000.0; R0603
R39: 75000.0; R0603
R42, R43: 95300.0; R0603
R47: 86418.181818182; R0603
U1: STM32F767IIT6; LQFP176
U2: FT232RL-REEL; SSOP-28
U3: 10118193-0001LF; FCI_10118193-0001LF
U4: MAX3218EAP+T; SSOP-20
U5, U10: HTSS-105-01-G-D
U6: mtfc4gmcdm; TFBGA-153
U7: SP3203ECY-L/TR; TSSOP20-I
U8: 182-009-113R531; 182-009-MALE
U9: ST3241EBPR; SSOP-28
U11: ABS07-32.768KHZ-7-T
U12: ABLS-25.000MHZ-B2F-T
U13: ASFL1-12MHZ-NCS; ASFL1
U14, U16: LP3878SDX-ADJ/NOPB; WSON-8
U15: LTC3601EUD#PBF; QFN-16_EP
U17: LTC2928CUHF#PBF; QFN-38_UHF
U18, U19: IRF8306MTRPbF; IRF8306MTRPBF
U20: 4-1437565-2; SW_4-1437565-2
U21: Q65110A2395; LGM67K-G1J2-24-Z
U22, U23: nc7sz125m5x; NC7SZ125M5X

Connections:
CLK_CRYSTAL_U1_9: C25.1, U1.9, U11.1
CLK_CRYSTAL_U1_10: C26.1, U1.10, U11.2
CLK_CRYSTAL_U1_29: C27.1, U1.29, U12.1
CLK_CRYSTAL_U1_30: C28.1, U1.30, U12.2
CLK_U2_27: U2.27, U13.3
GND: C1.2, C2.2, C3.2, C4.2, C5.2, C6.2, C7.2, C8.2, C9.2, C10.2, C11.2, C12.2, C13.2, C14.2, C15.2, C16.2, C17.2, C18.2, C19.2, C20.2, C21.2, C22.2, C23.2, C24.2, C25.2, C26.2, C27.2, C28.2, C29.2, C30.2, C31.2, C32.2, C33.2, C34.2, C35.2, C37.2, C38.2, C39.2, C40.2, C41.2, C42.2, C43.2, C44.2, C47.2, C48.2, C49.2, C52.2, C53.2, C54.2, C55.2, C56.2, C57.2, C58.2, C59.2, C61.1, C61.2, C62.2, C63.2, C64.2, C65.2, C66.2, C67.2, C68.2, C69.2, C70.2, C71.2, C72.2, C73.2, J1.2, R2.2, R9.2, R14.2, R31.2, R32.2, R34.2, R37.2, R39.2, R42.2, R43.2, R44.2, R45.2, R46.2, U1.14, U1.22, U1.37, U1.61, U1.71, U1.90, U1.102, U1.113, U1.126, U1.135, U1.148, U1.158, U2.7, U2.18, U2.21, U2.25, U2.26, U3.5, U3.6, U3.7, U3.8, U3.9, U4.5, U4.17, U4.20, U5.9, U6.C4, U6.E7, U6.G5, U6.H10, U6.K8, U6.N2, U6.N5, U6.P4, U6.P6, U7.18, U8.5, U9.23, U9.25, U10.9, U13.2, U14.3, U14.PAD, U15.1, U15.9, U15.17, U16.3, U16.PAD, U17.8, U17.9, U17.10, U17.12, U17.13, U17.24, U17.25, U17.30, U17.32, U17.39, U21.C, U22.1, U22.3, U23.1, U23.3
NET_U1_31: R8.1, U1.31, U23.4
NET_U1_39: C20.1, C21.1, F1.1, U1.38, U1.39
NET_U1_48: R11.1, U1.48
NET_U1_125: C24.1, U1.125
NET_U1_166: R9.1, U1.166
NET_U1_171: R10.1, U1.171
NET_U1_176: U20.3, U20.4
NET_U2_14: R13.1, U2.14
NET_U2_17: C31.1, U2.17
NET_U2_19: R14.1, U2.19
NET_U3_1: R12.1, U3.1
NET_U3_2: U2.16, U3.2
NET_U3_3: U2.15, U3.3
NET_U4_1: I1.1, U4.1
NET_U4_2: R15.1, U4.2
NET_U4_3: R16.1, U4.3
NET_U4_4: R17.1, U4.4
NET_U4_15: C35.1, U4.15
NET_U4_16: C36.2, U4.16
NET_U4_18: C36.1, U4.18
NET_U4_19: C34.1, U4.19
NET_U5_3: U4.12, U5.3
NET_U5_4: U4.11, U5.4
NET_U5_5: U4.14, U5.5
NET_U5_6: U4.13, U5.6
NET_U6_C2: C39.1, C40.1, U6.C2
NET_U6_K5: R7.1, U6.K5, U22.4
NET_U7_1: C45.1, U7.1
NET_U7_2: C47.1, U7.2
NET_U7_3: C45.2, U7.3
NET_U7_4: C46.1, U7.4
NET_U7_5: C46.2, U7.5
NET_U7_6: C48.1, U7.6
NET_U8_2: U7.14, U8.2
NET_U8_3: U7.17, U8.3
NET_U8_7: U7.13, U8.7
NET_U8_8: U7.16, U8.8
NET_U9_1: C51.1, U9.1
NET_U9_2: C51.2, U9.2
NET_U9_3: C53.1, U9.3
NET_U9_22: R28.1, U9.22
NET_U9_24: C50.2, U9.24
NET_U9_27: C52.1, U9.27
NET_U9_28: C50.1, U9.28
NET_U10_3: U9.4, U10.3
NET_U10_4: U9.5, U10.4
NET_U10_5: U9.9, U10.5
NET_U10_6: U9.10, U10.6
NET_U14_1: C55.1, U14.1
NET_U14_6: R30.2, R31.1, U14.6
NET_U14_8: R29.1, U14.8
NET_U15_3: C60.2, I2.1, U15.3, U15.4
NET_U15_6: C60.1, U15.6
NET_U15_7: C59.1, U15.7, U15.12
NET_U15_10: R34.1, U15.10
NET_U15_11: R32.1, R33.1, U15.11
NET_U15_ATNET_3: I2.2, R33.2
NET_U16_1: C62.1, U16.1
NET_U16_6: R36.2, R37.1, U16.6
NET_U16_8: R35.1, U16.8
NET_U17_3: R45.1, U17.3
NET_U17_6: R42.1, U17.6
NET_U17_7: R43.1, U17.7
NET_U17_16: R44.1, R47.1, U17.16
NET_U17_18: R41.1, U17.18
NET_U17_19: R40.1, U17.19, U17.20
NET_U17_21: R38.1, R39.1, U17.21, U22.2, U23.2
NET_U17_22: C65.1, R38.2, R40.2, R41.2, U17.11, U17.22
NET_U17_26: C68.1, U17.26
NET_U17_27: C67.1, U17.27
NET_U17_28: C69.1, U17.28
NET_U17_38: R46.1, U17.38
NET_U18_3: U17.2, U18.3
NET_U19_3: U17.37, U19.3
NET_U20_1: R2.1, U20.1, U20.2
PROC_SDMMC1_CK: R27.1, U1.141, U6.M6
PROC_SDMMC1_CMD: R26.1, U1.144, U6.M5
PROC_SDMMC1_D0: R18.1, U1.117, U6.A3
PROC_SDMMC1_D1: R19.1, U1.118, U6.A4
PROC_SDMMC1_D2: R20.1, U1.139, U6.A5
PROC_SDMMC1_D3: R21.1, U1.140, U6.B2
PROC_SDMMC1_D4: R22.1, U1.167, U6.B3
PROC_SDMMC1_D5: R23.1, U1.168, U6.B4
PROC_SDMMC1_D6: R24.1, U1.115, U6.B5
PROC_SDMMC1_D7: R25.1, U1.116, U6.B6
PROC_UART4_CTS: U1.56, U7.8
PROC_UART4_RTS: U1.94, U7.10
PROC_UART4_RX: U1.11, U7.11
PROC_UART4_TX: U1.128, U7.7
PROC_UART7_CTS: U1.27, U4.8
PROC_UART7_RTS: U1.26, U4.10
PROC_UART7_RX: U1.24, U4.9
PROC_UART7_TX: U1.25, U4.7
PROC_UART8_CTS: U1.104, U2.3
PROC_UART8_RTS: U1.105, U2.11
PROC_UART8_RX: U1.169, U2.1
PROC_UART8_TX: U1.170, U2.5
PROC_USART1_CTS: U1.122, U9.13
PROC_USART1_RTS: U1.123, U9.18
PROC_USART1_RX: U1.95, U9.19
PROC_USART1_TX: U1.120, U9.14
VCC_10V8: C66.1, C70.1, C71.1, J1.1, R47.2, U17.23, U18.1, U18.2, U18.6, U18.7, U19.1, U19.2, U19.6, U19.7
VCC_S1_10V8: C56.1, C58.1, R29.2, U14.4, U15.15, U15.16, U18.4, U18.5
VCC_S2_10V8: C63.1, R35.2, U16.4, U19.4, U19.5
VCC_TIER1_1V2: C23.1, C57.1, R30.1, U1.81, U14.5
VCC_TIER1_3V3: C1.1, C2.1, C3.1, C4.1, C5.1, C6.1, C7.1, C8.1, C9.1, C10.1, C11.1, C12.1, C13.1, C14.1, C15.1, C16.1, C17.1, C18.1, C19.1, C22.1, C29.1, C30.1, C32.1, C33.1, C37.1, C38.1, C41.1, C42.1, C43.1, C44.1, C49.1, C54.1, C61.2, C72.1, C73.1, F1.2, I1.2, I2.2, R7.2, R8.2, R10.2, R11.2, R13.2, R15.2, R16.2, R17.2, R18.2, R19.2, R20.2, R21.2, R22.2, R23.2, R24.2, R25.2, R26.2, R27.2, R28.2, R33.2, U1.6, U1.15, U1.23, U1.36, U1.49, U1.62, U1.72, U1.82, U1.91, U1.103, U1.114, U1.127, U1.136, U1.149, U1.159, U1.172, U2.4, U2.20, U4.6, U6.C6, U6.E6, U6.F5, U6.J10, U6.K9, U6.M4, U6.N4, U6.P3, U6.P5, U7.12, U7.19, U9.26, U13.4, U15.8, U22.5, U23.5
VCC_TIER2_1V2: C64.1, R36.1, U16.5
